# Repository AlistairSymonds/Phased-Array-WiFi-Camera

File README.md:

# Phased-Array-WiFi-Camera

Still very much a work in progress, only making it public to share completed RF section. Don't look at the digital section too closely :P

Run in fpga dir

``fusesoc --cores-root . run --target=sim pawc``

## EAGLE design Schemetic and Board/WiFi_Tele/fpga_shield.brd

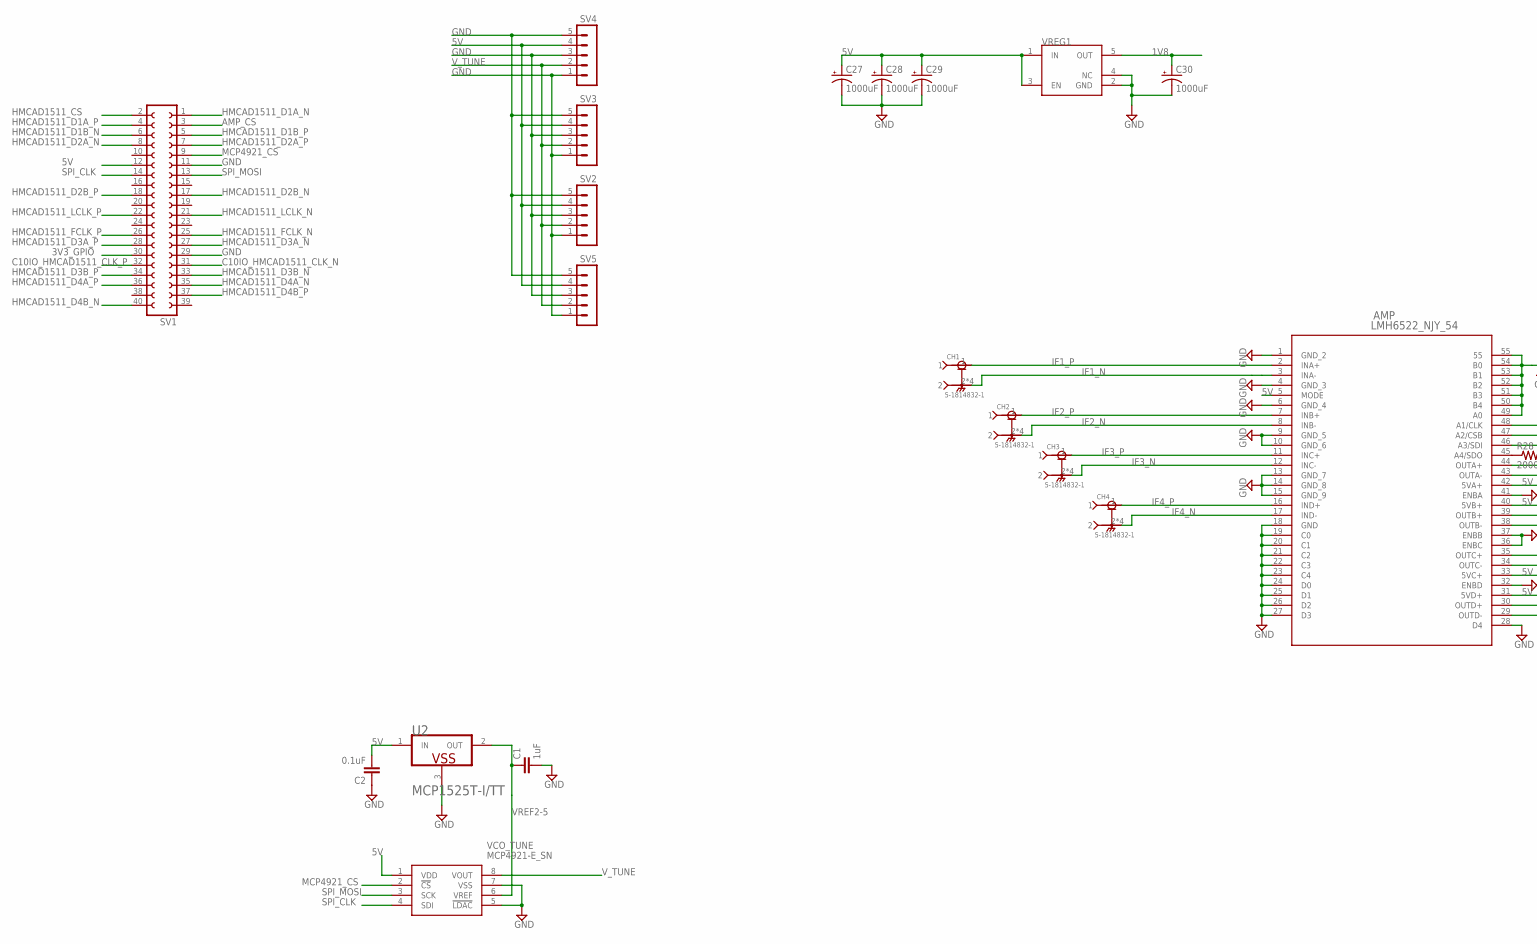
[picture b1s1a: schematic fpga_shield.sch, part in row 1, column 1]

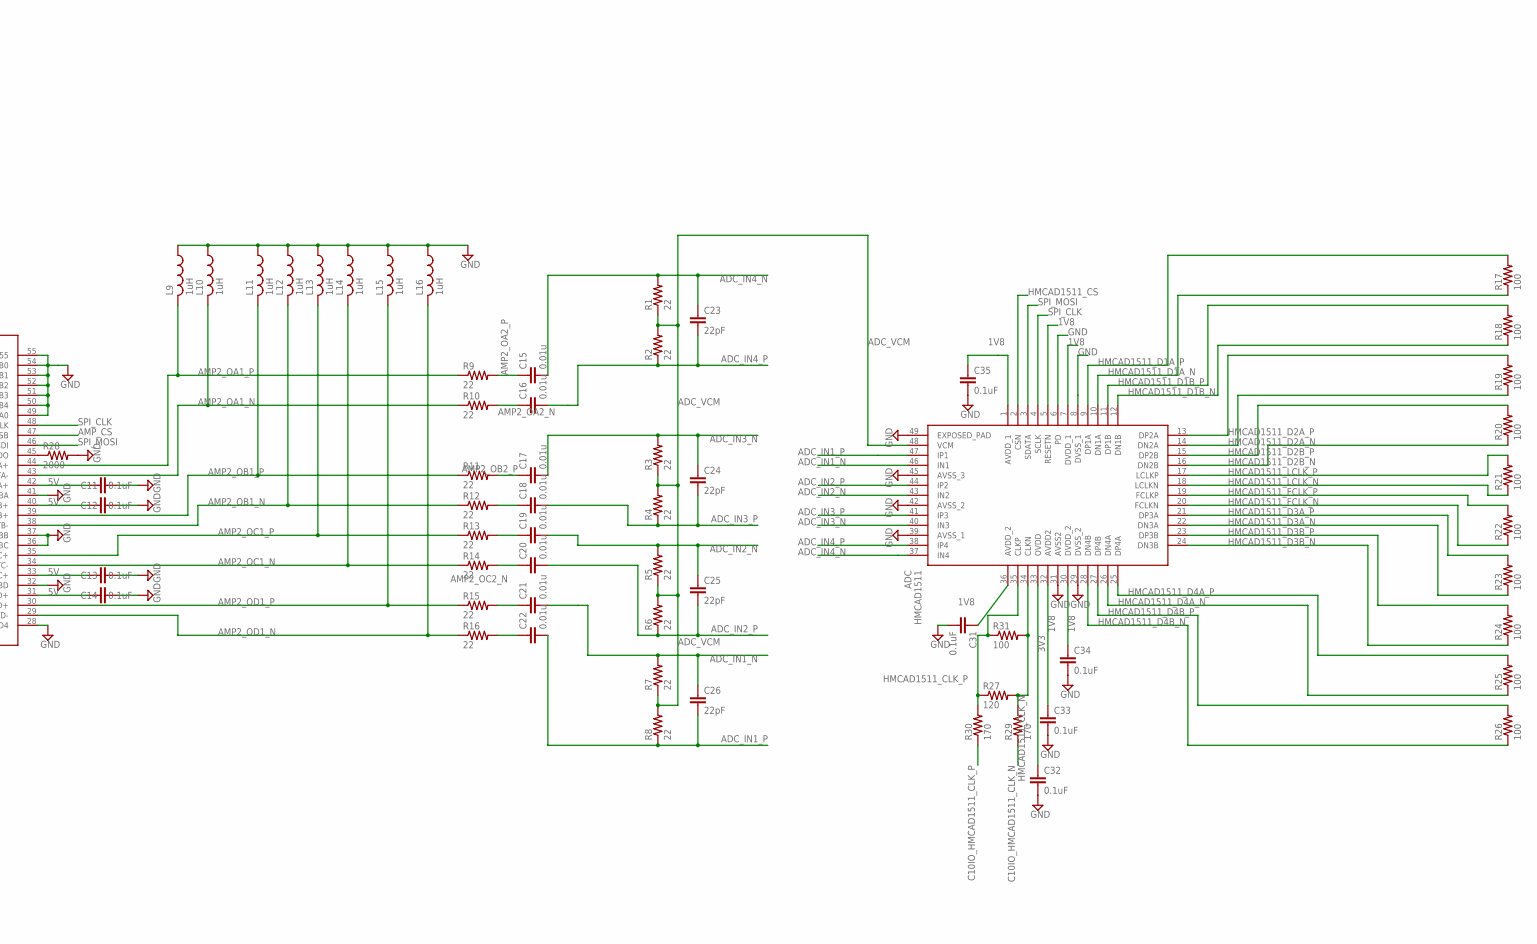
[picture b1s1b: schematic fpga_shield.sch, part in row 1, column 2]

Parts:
ADC: HMCAD1511; QFN50P700X700X100-49N
AMP: LMH6522_NJY_54; SQA54A
C1: 1uF; C0805
C2, C11, C12, C13, C14, C31, C32, C33, C34, C35: 0.1uF; C0805
C15, C16, C17, C18, C19, C20, C21, C22: 0.01u; C0805
C23, C24, C25, C26: 22pF; C0805
C27, C28, C29, C30: 1000uF; 150CLZ-1010
CH1, CH2, CH3, CH4: 5-1814832-1; TE_5-1814832-1
L9, L10, L11, L12, L13, L14, L15, L16: 1uH; INDC2518X180
R1, R2, R3, R4, R5, R6, R7, R8, R9, R10, R11, R12, R13, R14, R15, R16: 22; R0805
R17, R18, R19, R20, R21, R22, R23, R24, R25, R26, R31: 100; R0402
R27: 120; R0402
R28: 2000; R0805
R29, R30: 170; R0402
SV1: FE20-2
SV2, SV3, SV4, SV5: MA05-1
U2: MICROCHIP_MCP1525T-I-TTMICROCHIP_MCP1525T-I-TT_0_1; MICROCHIP_MCP1525T-I-TT_1
VCO_TUNE: MCP4921-E_SN; SOIC127P600X175-8N
VREG1: TLV75718PDBVR; SOT95P240X110-5

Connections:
1V8: ADC.1 (AVDD_1), ADC.5 (RESETN), ADC.7 (DVDD_1), ADC.30 (DVDD_2), ADC.32 (AVDD2), ADC.36 (AVDD_2), C30.+, C31.1, C33.1, C34.1, C35.1, VREG1.5 (OUT)
3V3: ADC.33 (OVDD), C32.1
3V3_GPIO: SV1.30
5V: AMP.5 (MODE), AMP.31 (5VD+), AMP.33 (5VC+), AMP.40 (5VB+), AMP.42 (5VA+), C2.2, C11.1, C12.1, C13.1, C14.1, C27.+, C28.+, C29.+, SV1.12, SV2.4, SV3.4, SV4.4, SV5.4, U2.1 (IN), VCO_TUNE.1 (VDD), VREG1.1 (IN), VREG1.3 (EN)
ADC_IN1_N: ADC.46 (IN1), C21.2, C26.1, R7.2
ADC_IN1_P: ADC.47 (IP1), C22.2, C26.2, R8.1
ADC_IN2_N: ADC.43 (IN2), C19.2, C25.1, R5.2
ADC_IN2_P: ADC.44 (IP2), C20.2, C25.2, R6.1
ADC_IN3_N: ADC.40 (IN3), C17.2, C24.1, R3.2
ADC_IN3_P: ADC.41 (IP3), C18.2, C24.2, R4.1
ADC_IN4_N: ADC.37 (IN4), C15.2, C23.1, R1.2
ADC_IN4_P: ADC.38 (IP4), C16.2, C23.2, R2.1
ADC_VCM: ADC.48 (VCM), R1.1, R2.2, R3.1, R4.2, R5.1, R6.2, R7.1, R8.2
AMP2_OA1_N: AMP.43 (OUTA-), L10.2, R10.1
AMP2_OA1_P: AMP.44 (OUTA+), L9.2, R9.1
AMP2_OA2_N: C16.1, R10.2
AMP2_OA2_P: C15.1, R9.2
AMP2_OB1_N: AMP.38 (OUTB-), L12.2, R12.1
AMP2_OB1_P: AMP.39 (OUTB+), L11.2, R11.1
AMP2_OB2_N: C18.1, R12.2
AMP2_OB2_P: C17.1, R11.2
AMP2_OC1_N: AMP.34 (OUTC-), L14.2, R14.1
AMP2_OC1_P: AMP.35 (OUTC+), L13.2, R13.1
AMP2_OC2_N: C20.1, R14.2
AMP2_OC2_P: C19.1, R13.2
AMP2_OD1_N: AMP.29 (OUTD-), L16.2, R16.1
AMP2_OD1_P: AMP.30 (OUTD+), L15.2, R15.1
AMP2_OD2_N: C22.1, R16.2
AMP2_OD2_P: C21.1, R15.2
AMP_CS: AMP.47 (A2/CSB), SV1.3
C10IO_HMCAD1511_CLK_N: R29.1, SV1.31
C10IO_HMCAD1511_CLK_P: R30.1, SV1.32
GND: ADC.6 (PD), ADC.8 (DVSS_1), ADC.29 (DVSS_2), ADC.31 (AVSS2), ADC.39 (AVSS_1), ADC.42 (AVSS_2), ADC.45 (AVSS_3), ADC.49 (EXPOSED_PAD), AMP.1 (GND_2), AMP.4 (GND_3), AMP.6 (GND_4), AMP.9 (GND_5), AMP.10 (GND_6), AMP.13 (GND_7), AMP.14 (GND_8), AMP.15 (GND_9), AMP.18 (GND), AMP.19 (C0), AMP.20 (C1), AMP.21 (C2), AMP.22 (C3), AMP.23 (C4), AMP.24 (D0), AMP.25 (D1), AMP.26 (D2), AMP.27 (D3), AMP.28 (D4), AMP.32 (ENBD), AMP.36 (ENBC), AMP.37 (ENBB), AMP.41 (ENBA), AMP.49 (A0), AMP.50 (B4), AMP.51 (B3), AMP.52 (B2), AMP.53 (B1), AMP.54 (B0), AMP.55, C1.2, C2.1, C11.2, C12.2, C13.2, C14.2, C27.-, C28.-, C29.-, C30.-, C31.2, C32.2, C33.2, C34.2, C35.2, L9.1, L10.1, L11.1, L12.1, L13.1, L14.1, L15.1, L16.1, R28.2, SV1.11, SV1.29, SV2.1, SV2.3, SV2.5, SV3.1, SV3.3, SV3.5, SV4.1, SV4.3, SV4.5, SV5.1, SV5.3, SV5.5, U2.3 (VSS), VCO_TUNE.5 (!LDAC), VCO_TUNE.7 (VSS), VREG1.2 (GND), VREG1.4 (NC)
HMCAD1511_CLK_N: ADC.34 (CLKN), R27.2, R29.2, R31.2
HMCAD1511_CLK_P: ADC.35 (CLKP), R27.1, R30.2, R31.1
HMCAD1511_CS: ADC.2 (CSN), SV1.2
HMCAD1511_D1A_N: ADC.10 (DN1A), R17.1, SV1.1
HMCAD1511_D1A_P: ADC.9 (DP1A), R17.2, SV1.4
HMCAD1511_D1B_N: ADC.12 (DN1B), R18.1, SV1.6
HMCAD1511_D1B_P: ADC.11 (DP1B), R18.2, SV1.5
HMCAD1511_D2A_N: ADC.14 (DN2A), R19.1, SV1.8
HMCAD1511_D2A_P: ADC.13 (DP2A), R19.2, SV1.7
HMCAD1511_D2B_N: ADC.16 (DN2B), R20.1, SV1.17
HMCAD1511_D2B_P: ADC.15 (DP2B), R20.2, SV1.18
HMCAD1511_D3A_N: ADC.22 (DN3A), R23.1, SV1.27
HMCAD1511_D3A_P: ADC.21 (DP3A), R23.2, SV1.28
HMCAD1511_D3B_N: ADC.24 (DN3B), R24.1, SV1.33
HMCAD1511_D3B_P: ADC.23 (DP3B), R24.2, SV1.34
HMCAD1511_D4A_N: ADC.26 (DN4A), R25.1, SV1.35
HMCAD1511_D4A_P: ADC.25 (DP4A), R25.2, SV1.36
HMCAD1511_D4B_N: ADC.28 (DN4B), R26.1, SV1.40
HMCAD1511_D4B_P: ADC.27 (DP4B), R26.2, SV1.37
HMCAD1511_FCLK_N: ADC.20 (FCLKN), R22.1, SV1.25
HMCAD1511_FCLK_P: ADC.19 (FCLKP), R22.2, SV1.26
HMCAD1511_LCLK_N: ADC.18 (LCLKN), R21.1, SV1.21
HMCAD1511_LCLK_P: ADC.17 (LCLKP), R21.2, SV1.22
IF1_N: AMP.3 (INA-), CH1.2, CH1.3 (2), CH1.4 (2), CH1.5 (2)
IF1_P: AMP.2 (INA+), CH1.1
IF2_N: AMP.8 (INB-), CH2.2, CH2.3 (2), CH2.4 (2), CH2.5 (2)
IF2_P: AMP.7 (INB+), CH2.1
IF3_N: AMP.12 (INC-), CH3.2, CH3.3 (2), CH3.4 (2), CH3.5 (2)
IF3_P: AMP.11 (INC+), CH3.1
IF4_N: AMP.17 (IND-), CH4.2, CH4.3 (2), CH4.4 (2), CH4.5 (2)
IF4_P: AMP.16 (IND+), CH4.1
MCP4921_CS: SV1.9, VCO_TUNE.2 (!CS)
unnamed: AMP.45 (A4/SDO), R28.1
SPI_CLK: ADC.4 (SCLK), AMP.48 (A1/CLK), SV1.14, VCO_TUNE.4 (SDI)
SPI_MOSI: ADC.3 (SDATA), AMP.46 (A3/SDI), SV1.13, VCO_TUNE.3 (SCK)
VREF2-5: C1.1, U2.2 (OUT), VCO_TUNE.6 (VREF)
V_TUNE: SV2.2, SV3.2, SV4.2, SV5.2, VCO_TUNE.8 (VOUT)

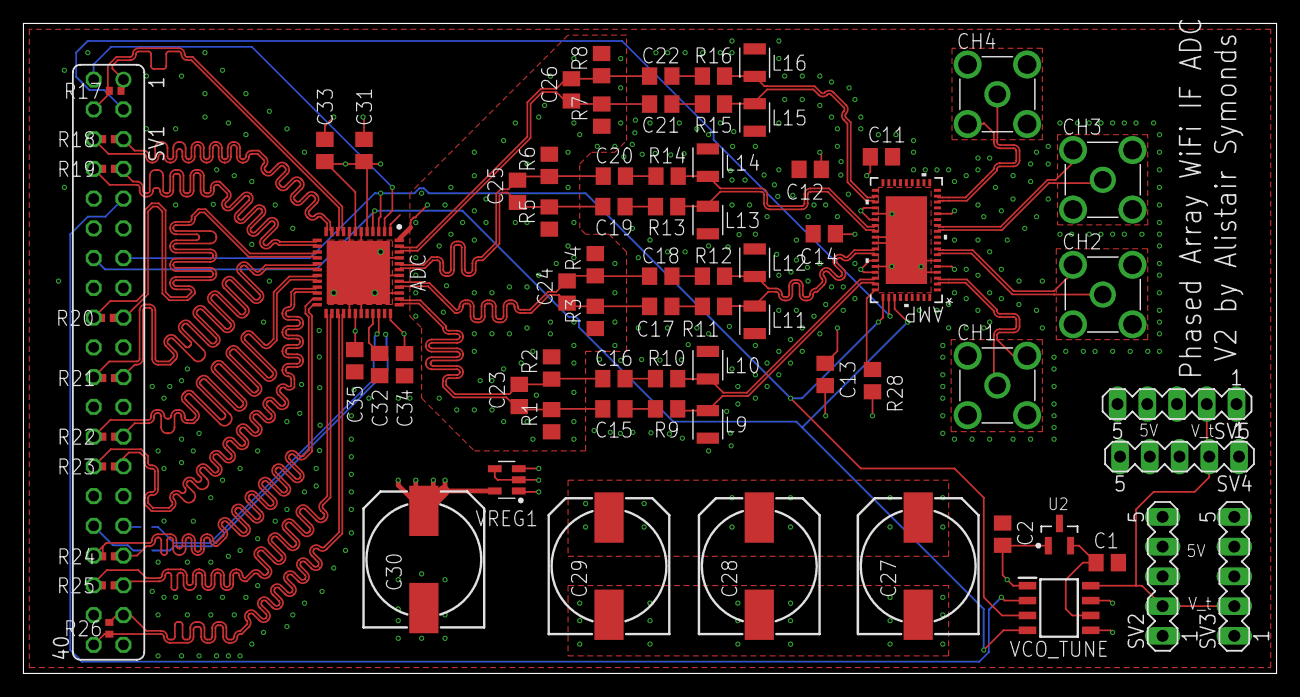
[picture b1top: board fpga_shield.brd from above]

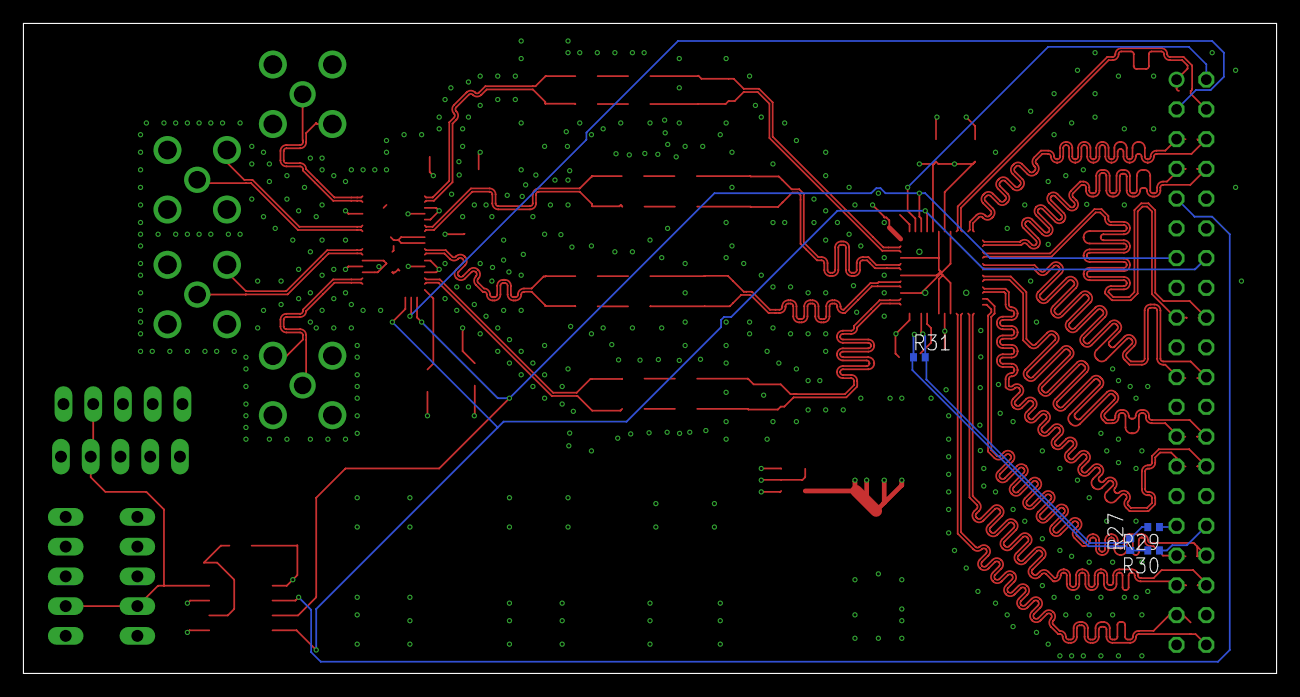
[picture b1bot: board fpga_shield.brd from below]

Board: 4 copper layers, 107.0 x 55.5 mm, 80 parts (4 on the bottom side), 69 nets.

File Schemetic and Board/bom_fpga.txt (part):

Partlist

Exported from fpga_shield.brd at 10/08/2018 2:50 PM

EAGLE Version 9.1.2 Copyright (c) 1988-2018 Autodesk, Inc.

Assembly variant: 

Part     Value                                              Package                   Library      Position (mm)         Orientation

ADC      HMCAD1511                                          QFN50P700X700X100-49N     HMCAD1511    (28.59 34.23)         R270
AMP      LMH6522_NJY_54                                     SQA54A                    LMH6522      (75.39 37)            R180
C1       1uF                                                C0805                     rcl          (92.54 9.46)          R0
C2       0.1uF                                              C0805                     rcl          (83.61 11.89)         R270
C11      0.1uF                                              C0805                     rcl          (73.26 44.11)         R0
C12      0.1uF                                              C0805                     rcl          (67.18 43.04)         R180
C13      0.1uF                                              C0805                     rcl          (68.46 25.53)         R270
C14      0.1uF                                              C0805                     rcl          (68.38 37.54)         R180
C15      0.01u                                              C0805                     rcl          (50.42 22.59)         R180
C16      0.01u                                              C0805                     rcl          (50.42 25.17)         R180
C17      0.01u                                              C0805                     rcl          (54.42 31.34)         R180
C18      0.01u                                              C0805                     rcl          (54.42 33.92)         R180
C19      0.01u                                              C0805                     rcl          (50.42 39.8575)       R180
C20      0.01u                                              C0805                     rcl          (50.458 42.462)       R180
C21      0.01u                                              C0805                     rcl          (54.42 48.6175)       R180
C22      0.01u                                              C0805                     rcl          (54.42 51.0025)       R180
C23      22pF                                               C0805                     rcl          (42.336 23.731)       R90
C24      22pF                                               C0805                     rcl          (46.418 32.564665625) R90
C25      22pF                                               C0805                     rcl          (42.185 41.16733125)  R90
C26      22pF                                               C0805                     rcl          (46.789 49.823996875) R90
C27      1000uF                                             150CLZ-1010               rcl          (76.4 9.16)           R90
C28      1000uF                                             150CLZ-1010               rcl          (62.83 9.16)          R90
C29      1000uF                                             150CLZ-1010               rcl          (50 9.16)             R90
C30      1000uF                                             150CLZ-1010               rcl          (34.19 9.73)          R90
C31      0.1uF                                              C0805                     rcl          (29.08 44.65)         R90
C32      0.1uF                                              C0805                     rcl          (32.16 44.65)         R90
C33      0.1uF                                              C0805                     rcl          (25.74 44.65)         R90
C34      0.1uF                                              C0805                     rcl          (32.542 25.863)       R270
C35      0.1uF                                              C0805                     rcl          (28.792 25.701)       R270
CH1      5-1814832-1                                        TE_5-1814832-1            5-1814832-1  (83.16 24.59)         R0
CH2      5-1814832-1                                        TE_5-1814832-1            5-1814832-1  (92.16 32.35)         R0
CH3      5-1814832-1                                        TE_5-1814832-1            5-1814832-1  (92.16 42.15)         R0
CH4      5-1814832-1                                        TE_5-1814832-1            5-1814832-1  (83.16 49.45)         R0
L9       1uH                                                INDC2518X180              Passives     (58.44 21.2625)       R90
L10      1uH                                                INDC2518X180              Passives     (58.44 26.3175)       R270
L11      1uH                                                INDC2518X180              Passives     (62.44 30.1925)       R90
L12      1uH                                                INDC2518X180              Passives     (62.44 35.0675)       R270
L13      1uH                                                INDC2518X180              Passives     (58.44 38.71)         R90
L14      1uH                                                INDC2518X180              Passives     (58.44 43.6095)       R270
L15      1uH                                                INDC2518X180              Passives     (62.44 47.47)         R90
L16      1uH                                                INDC2518X180              Passives     (62.44 52.15)         R270
R1       22                                                 R0805                     rcl          (45.1 21.58)          R90
R2       22                                                 R0805                     rcl          (45.1 26.08)          R90
R3       22                                                 R0805                     rcl          (48.828 30.398)       R90
R4       22                                                 R0805                     rcl          (48.828 34.898)       R90
R5       22                                                 R0805                     rcl          (44.902 38.882)       R90
R6       22                                                 R0805                     rcl          (44.902 43.382)       R90
R7       22                                                 R0805                     rcl          (49.386 47.671)       R90
R8       22                                                 R0805                     rcl          (49.366 51.984)       R90
R9       22                                                 R0805                     rcl          (54.92 22.59)         R180
R10      22                                                 R0805                     rcl          (54.92 25.17)         R180
R11      22                                                 R0805                     rcl          (58.92 31.34)         R180
R12      22                                                 R0805                     rcl          (58.92 33.92)         R180
R13      22                                                 R0805                     rcl          (54.92 39.8575)       R180
R14      22                                                 R0805                     rcl          (54.958 42.462)       R180
R15      22                                                 R0805                     rcl          (58.92 48.6175)       R180
R16      22                                                 R0805                     rcl          (58.92 51.0025)       R180
R17      100                                                R0603                     rcl          (12.04 48.98)         R270
R18      100                                                R0603                     rcl          (2.56 48.15)          R90
R19      100                                                R0603                     rcl          (2.37 44.15)          R90
R20      100                                                R0603                     rcl          (2.68 30.15)          R90
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
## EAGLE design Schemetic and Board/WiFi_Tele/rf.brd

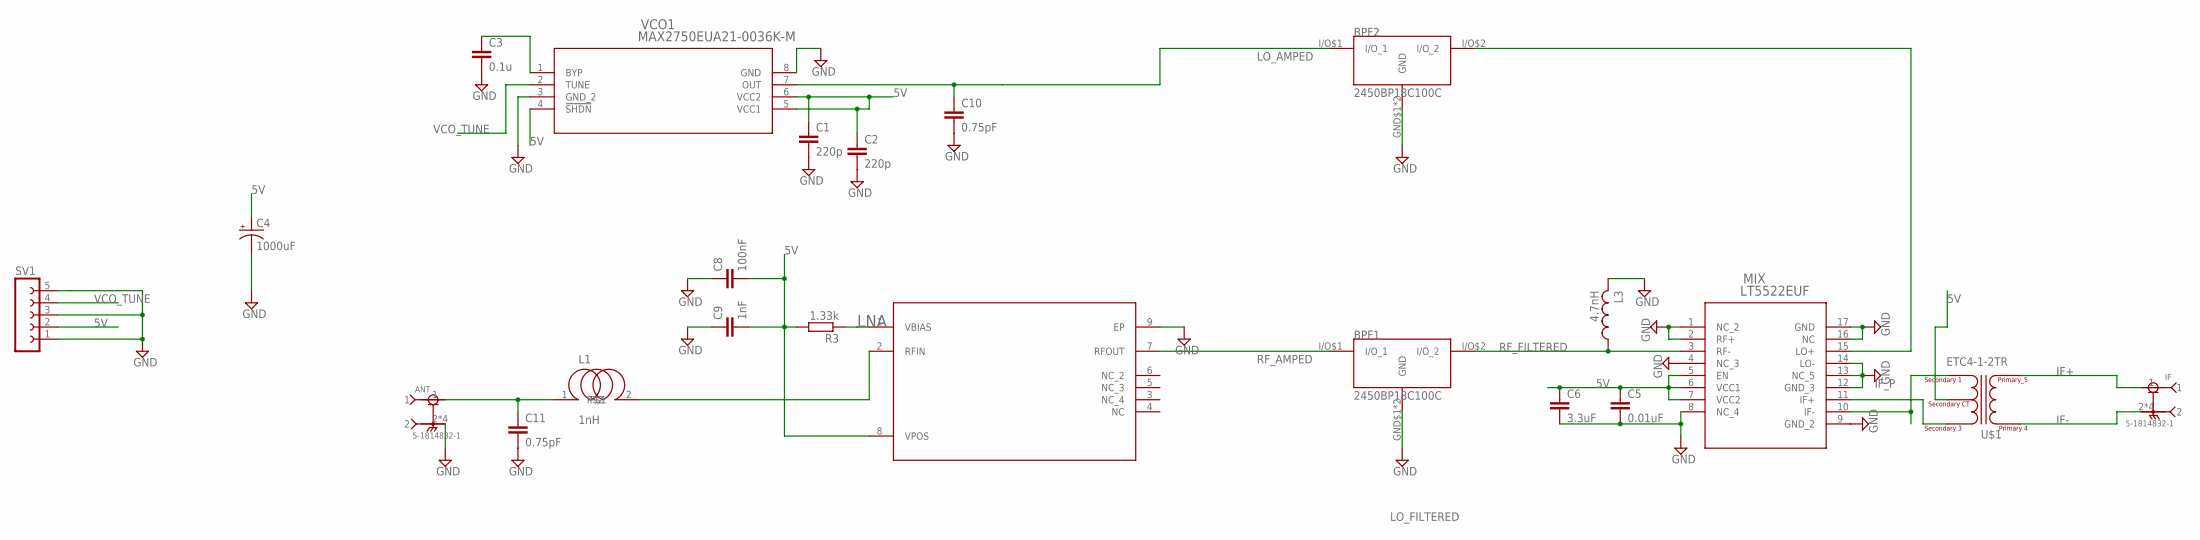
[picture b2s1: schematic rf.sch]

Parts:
ANT: 5-1814832-1; TE_5-1814832-1
BPF1, BPF2: 2450BP18C100C; SMD
C1, C2: 220p; C0805K
C3: 0.1u; C0805
C4: 1000uF; 153CLV-1010
C5: 0.01uF; C0805
C6: 3.3uF; C0805
C8: 100nF; C0805
C9: 1nF; C0805
C10, C11: 0.75pF; C0805
IF: 5-1814832-1; TE_5-1814832-1
L1: 1nH; INDC1607X61
L3: 4.7nH; INDC2518X180
LNA: ADL5523ACPZ-R7CP_8_2-M; CP_8_2-M
MIX: LT5522EUF; QFN-16_UF
R3: 1.33k; R0805
SV1: FE05-1
U$1: ETC4-1-2TR; SM-22
VCO1: MAX2750EUA21-0036K-M; 21-0036K-M

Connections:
5V: C1.1, C2.1, C4.+, C5.1, C6.1, C8.2, C9.2, LNA.8 (VPOS), MIX.5 (EN), MIX.6 (VCC1), MIX.7 (VCC2), R3.2, SV1.2, U$1.2 (SECONDARY_CT), VCO1.4 (!SHDN), VCO1.5 (VCC1), VCO1.6 (VCC2)
ANTENNA_IN: ANT.1, C11.1, L1.1
GND: ANT.2, ANT.3 (2), ANT.4 (2), ANT.5 (2), BPF1.GND$1 (GND), BPF1.GND$2 (GND), BPF2.GND$1 (GND), BPF2.GND$2 (GND), C1.2, C2.2, C3.2, C4.-, C5.2, C6.2, C8.1, C9.1, C10.2, C11.2, L3.2, LNA.9 (EP), MIX.1 (NC_2), MIX.2 (RF+), MIX.4 (NC_3), MIX.8 (NC_4), MIX.9 (GND_2), MIX.12 (GND_3), MIX.13 (NC_5), MIX.14 (LO-), MIX.16 (NC), MIX.17 (GND), SV1.1, SV1.3, SV1.5, VCO1.3 (GND_2), VCO1.8 (GND)
IF+: IF.1, U$1.5 (PRIMARY_5)
IF-: IF.2, IF.3 (2), IF.4 (2), IF.5 (2), U$1.4 (PRIMARY_4)
IF_P: MIX.11 (IF+), U$1.3 (SECONDARY_3)
LO_AMPED: BPF2.I/O$1 (I/O_1), C10.1, VCO1.7 (OUT)
LO_FILTERED: BPF2.I/O$2 (I/O_2), MIX.15 (LO+)
unnamed: LNA.1 (VBIAS), R3.1
unnamed: C3.1, VCO1.1 (BYP)
unnamed: MIX.10 (IF-), U$1.1 (SECONDARY_1)
unnamed: L1.2, LNA.2 (RFIN)
RF_AMPED: BPF1.I/O$1 (I/O_1), LNA.7 (RFOUT)
RF_FILTERED: BPF1.I/O$2 (I/O_2), L3.1, MIX.3 (RF-)
VCO_TUNE: SV1.4, VCO1.2 (TUNE)

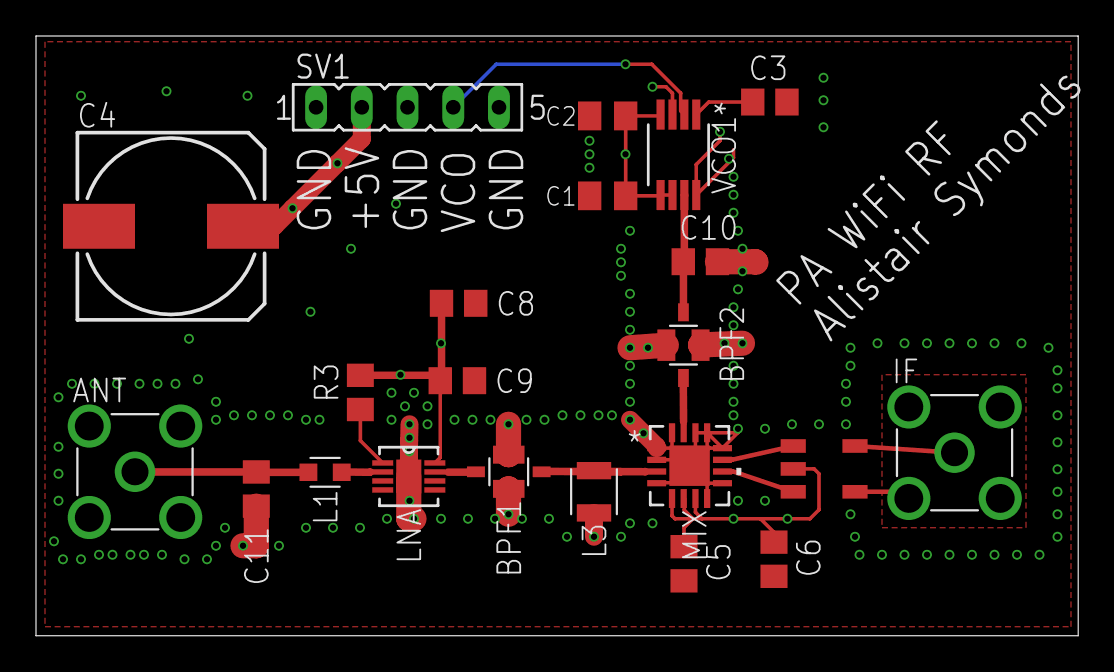
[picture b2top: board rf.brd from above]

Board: 4 copper layers, 57.9 x 33.3 mm, 22 parts (0 on the bottom side), 15 nets.

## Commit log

2018-08-06 more stuff
2018-08-08 changed mixer
    Changed mixer from HMC213B to LT5522 due to stock issues
2018-08-08 rf schematic v2
2018-08-08 Start FPGA board routing
    Routed SMA -> VGA1 matched diff pairs
2018-08-10 completed two VGA routing
2018-08-11 board complete and send for manufacturing
2018-08-13 switched over to Qsys for top level design
2018-08-15 working nios jtag uart
2018-08-15 Working NiosII SPI
2018-08-20 begun Intel TSE integration and testing
2018-08-20 TSE reg config and enable
2018-09-10 cleaned repo + first public for rf post
2018-10-31 Antenna design & Testing results
2018-11-01 Antenna Data
2020-02-17 Added new fpga project flow to use FuseSoC
2020-02-23 Deleted a whole bunch of stuff which shouldn't be in the repo
2020-02-23 Added booting picorv32
2020-02-23 fix typo
2020-02-24 Added basic FW makefile
2020-04-06 Added FW compile flow to fusesoc
2020-04-06 Updated simulation cmpnts to closer match HW
2020-04-07 Added GPIO block - output only
2020-08-19 Add basic ttrace analysis/beamforming jupyter NB
